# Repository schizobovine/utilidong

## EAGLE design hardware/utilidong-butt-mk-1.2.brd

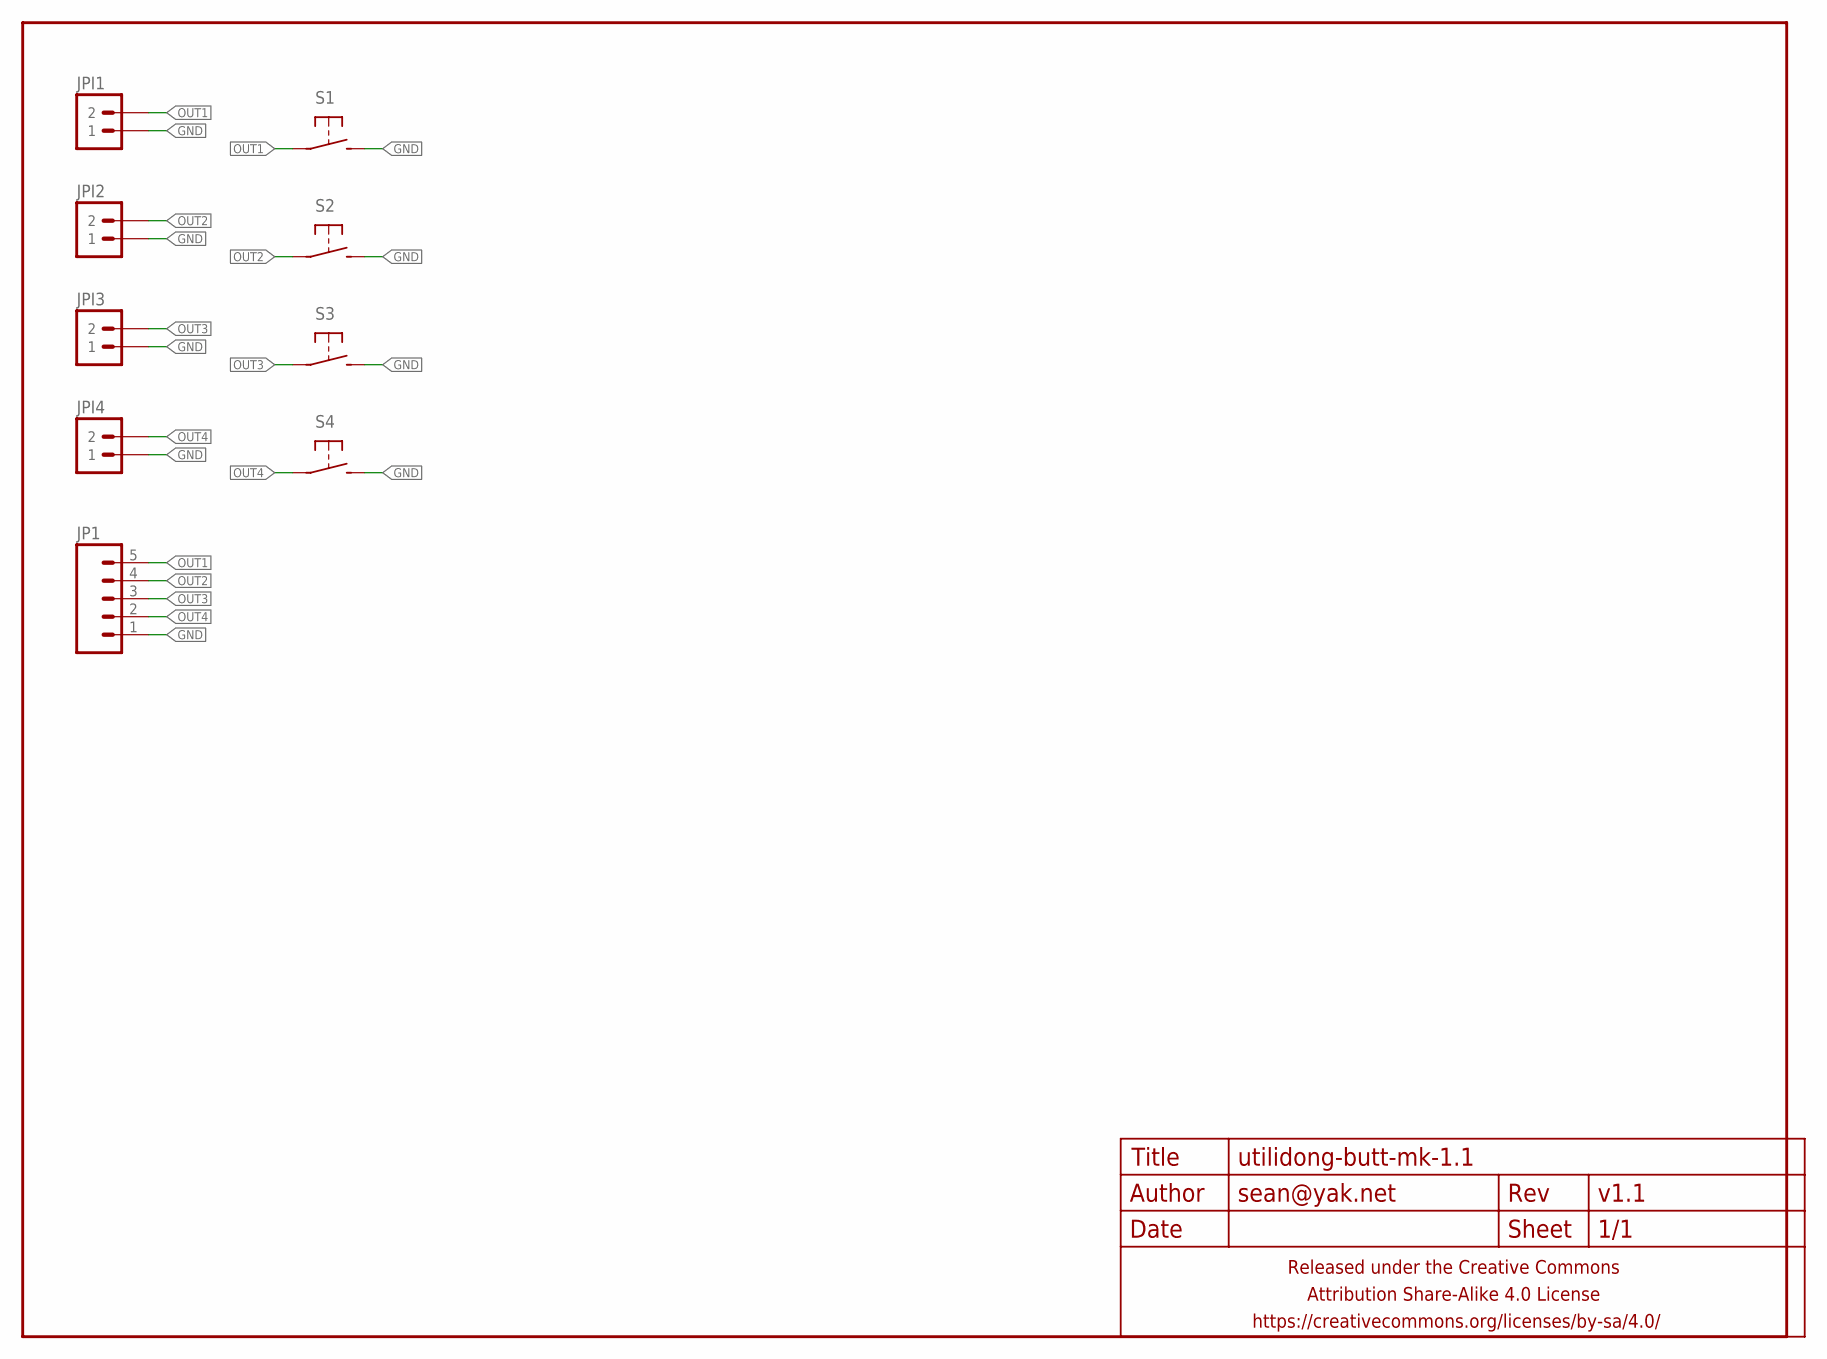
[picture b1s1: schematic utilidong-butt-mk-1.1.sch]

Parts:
FRAME1: FRAME-LETTERNO_PACKAGE; DUMMY
JP1: M05JST-PH-VERT-PTH; JST-5-PH-VERT-PTH
JPI1, JPI2, JPI3, JPI4: M02PTH-CENTERED; 1X02-CENTER
S1, S2, S3, S4: SPST-NO-TACT6MM-PTH-SMALL-PADS; DTS-6-SMALL-PADS

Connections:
GND: JP1.1, JPI1.1, JPI2.1, JPI3.1, JPI4.1, S1.3 (2), S1.4 (2), S2.3 (2), S2.4 (2), S3.3 (2), S3.4 (2), S4.3 (2), S4.4 (2)
OUT1: JP1.5, JPI1.2, S1.1, S1.2 (1)
OUT2: JP1.4, JPI2.2, S2.1, S2.2 (1)
OUT3: JP1.3, JPI3.2, S3.1, S3.2 (1)
OUT4: JP1.2, JPI4.2, S4.1, S4.2 (1)

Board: 2 copper layers, 10 parts (0 on the bottom side), 5 nets, no tracks yet.

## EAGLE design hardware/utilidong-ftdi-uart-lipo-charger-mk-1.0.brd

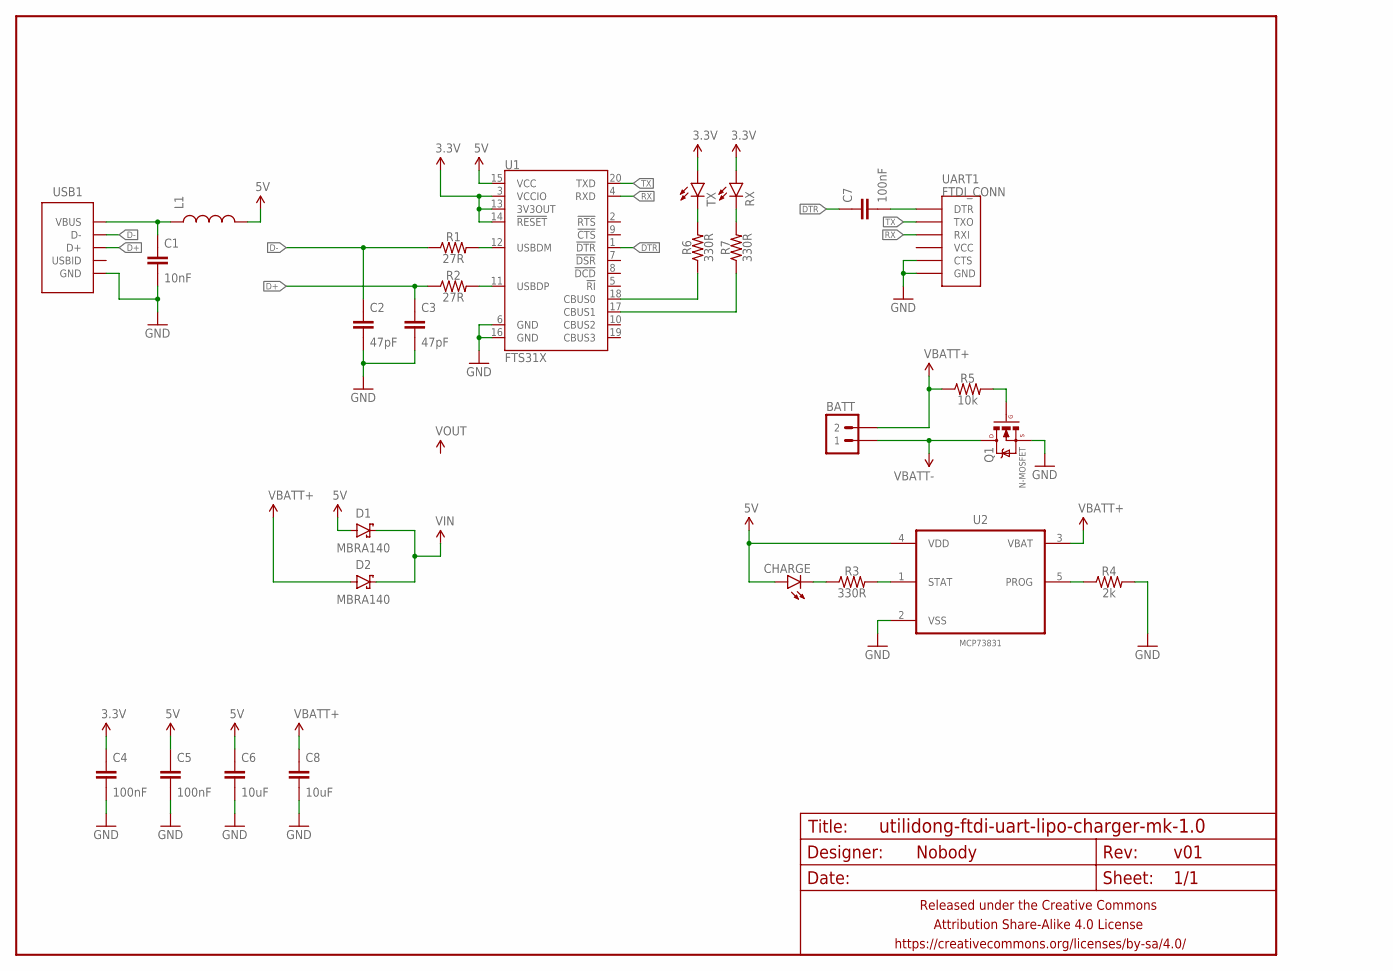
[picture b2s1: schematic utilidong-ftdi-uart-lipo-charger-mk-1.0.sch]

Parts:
BATT: M02PTH-CENTERED-R+; 1X02-CENTER-R+
C1: 10nF; C0805
C2, C3: 47pF; C0805
C4, C5, C7: 100nF; C0805
C6, C8: 10uF; C0805
CHARGE: LED1206; LED-1206
D1, D2: MBRA140; SMA-DIODE
FRAME1: FRAME-LETTERNO_PACKAGE; DUMMY
L1: INDUCTORL0805; L0805
Q1: N-MOSFET; SOT23
R1, R2: 27R; R0805
R3, R6, R7: 330R; R0805
R4: 2k; R0805
R5: 10k; R0805
RX: LED1206; LED-1206
TX: LED1206; LED-1206
U1: FTS31X; SSOP20_L
U2: MCP73831; SOT95P280X145-5N
UART1: FTDI_CONN
USB1: USB-ABCOMBO; USB-MICRO-B-FCI-CUTOUT

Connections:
3.3V: C4.1, RX.A, TX.A, U1.3 (VCCIO), U1.13 (3V3OUT), U1.14 (!RESET)
5V: C5.1, C6.1, CHARGE.A, D1.A, L1.2, U1.15 (VCC), U2.4 (VDD)
D+: C3.1, R2.1, USB1.3 (D+)
D-: C2.1, R1.1, USB1.2 (D-)
DTR: C7.1, U1.1 (!DTR)
GND: C1.2, C2.2, C3.2, C4.2, C5.2, C6.2, C8.2, Q1.2 (S), R4.2, U1.6 (GND), U1.16 (GND), U2.2 (VSS), UART1.CTS, UART1.GND, USB1.5 (GND), USB1.P$1 (GND), USB1.P$2 (GND)
unnamed: R1.2, U1.12 (USBDM)
unnamed: R2.2, U1.11 (USBDP)
unnamed: C1.1, L1.1, USB1.1 (VBUS)
unnamed: C7.2, UART1.DTR
unnamed: R3.2, U2.1 (STAT)
unnamed: CHARGE.C, R3.1
unnamed: R6.1, U1.18 (CBUS0)
unnamed: R4.1, U2.5 (PROG)
unnamed: R6.2, TX.C
unnamed: R7.2, RX.C
unnamed: Q1.1 (G), R5.2
unnamed: R7.1, U1.17 (CBUS1)
RX: U1.4 (RXD), UART1.RXI
TX: U1.20 (TXD), UART1.TXO
VBATT+: BATT.2, C8.1, D2.A, R5.1, U2.3 (VBAT)
VBATT-: BATT.1, Q1.3 (D)
VIN: D1.C, D2.C

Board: 2 copper layers, 28 parts (0 on the bottom side), 23 nets, no tracks yet.

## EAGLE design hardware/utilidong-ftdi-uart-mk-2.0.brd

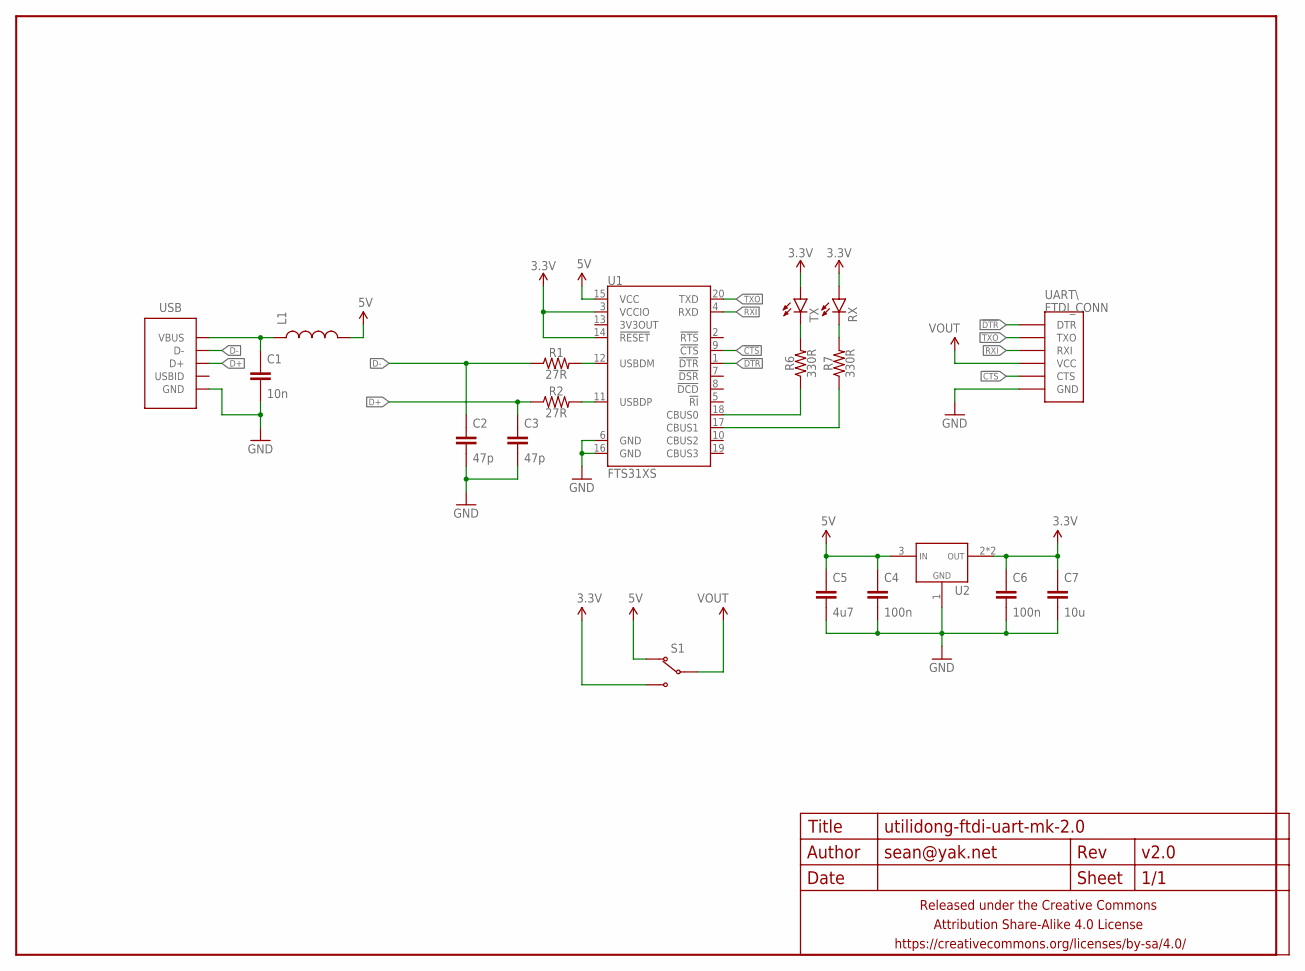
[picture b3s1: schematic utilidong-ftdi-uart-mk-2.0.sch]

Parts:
C1: 10n; C0603
C2, C3: 47p; C0603
C4, C6: 100n; C0603
C5: 4u7; C0603
C7: 10u; C0805
FRAME1: FRAME-LETTERNO_PACKAGE; DUMMY
L1: INDUCTOR0603; 0603
R1, R2: 27R; R0603
R6, R7: 330R; R0603
RX: LED0603; LED-0603
S1: SWITCH-SPDTSMD-RA; SWITCH-SPDT-SMD-RA
TX: LED0603; LED-0603
U1: FTS31XS; SSOP20_L
U2: VREG_1117SOT89; SOT89
UART\: FTDI_CONN
USB: USB-ABFCI-10103594-USB-MICRO-B-LESS; FCI-10103594-USB-MICRO-B-LESS

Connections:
3.3V: C6.1, C7.1, RX.A, S1.1 (NO), TX.A, U1.3 (VCCIO), U1.14 (!RESET), U2.2 (VOUT), U2.4 (VOUT)
5V: C4.1, C5.1, L1.2, S1.3 (NC), U1.15 (VCC), U2.3 (VIN)
!CTS: U1.9 (!CTS), UART\.CTS
!DTR: U1.1 (!DTR), UART\.DTR
D+: C3.1, R2.1, USB.3 (D+)
D-: C2.1, R1.1, USB.2 (D-)
GND: C1.2, C2.2, C3.2, C4.2, C5.2, C6.2, C7.2, U1.6 (GND), U1.16 (GND), U2.1 (GND), UART\.GND, USB.5 (GND)
unnamed: R1.2, U1.12 (USBDM)
unnamed: R2.2, U1.11 (USBDP)
unnamed: C1.1, L1.1, USB.1 (VBUS)
unnamed: R6.1, U1.18 (CBUS0)
unnamed: R6.2, TX.C
unnamed: R7.2, RX.C
unnamed: R7.1, U1.17 (CBUS1)
RXI: U1.4 (RXD), UART\.RXI
TXO: U1.20 (TXD), UART\.TXO
VOUT: S1.2 (COM), UART\.VCC

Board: 2 copper layers, 23 parts (3 on the bottom side), 17 nets, no tracks yet.

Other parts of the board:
U$3: COW_SMALL
U$4: CC-BY-SA-4.0-NO-URL
U$6: OSHWLOGO_TOP_0.2_A

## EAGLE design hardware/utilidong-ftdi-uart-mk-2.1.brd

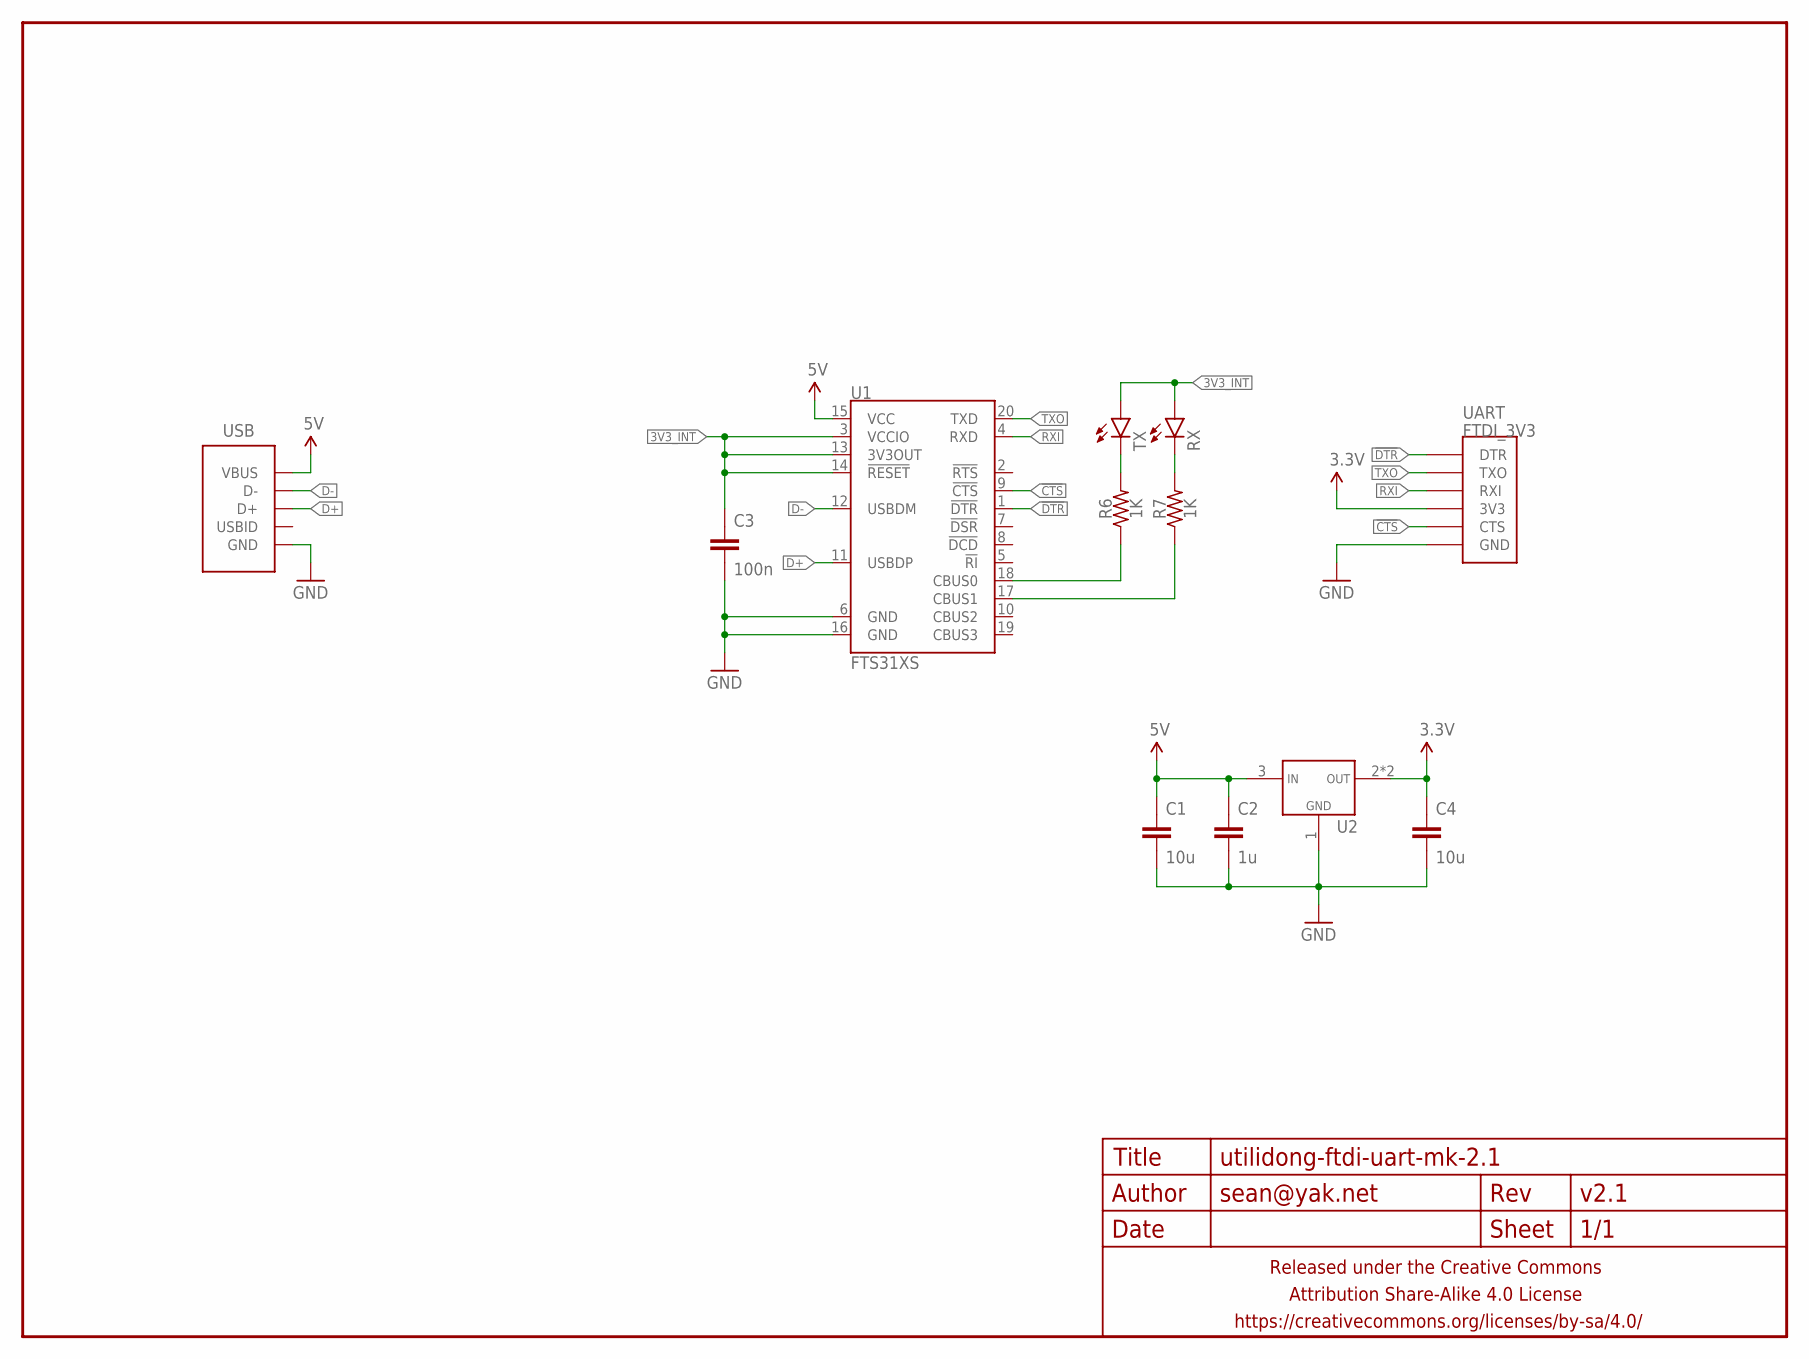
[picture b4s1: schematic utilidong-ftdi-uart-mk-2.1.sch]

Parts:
C1, C4: 10u; C0805
C2: 1u; C0603
C3: 100n; C0603
FRAME1: FRAME-LETTERNO_PACKAGE; DUMMY
R6, R7: 1K; R0603
RX: LED0603; LED-0603
TX: LED0603; LED-0603
U1: FTS31XS; SSOP20_L
U2: VREG_1117SOT89; SOT89
UART: FTDI_3V3
USB: USB-ABFCI-10103594-USB-MICRO-B-LESS; FCI-10103594-USB-MICRO-B-LESS

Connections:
3.3V: C4.1, U2.2 (VOUT), U2.4 (VOUT), UART.P$4 (3V3)
3V3_INT: C3.1, RX.A, TX.A, U1.3 (VCCIO), U1.13 (3V3OUT), U1.14 (!RESET)
5V: C1.1, C2.1, U1.15 (VCC), U2.3 (VIN), USB.1 (VBUS)
!CTS: U1.9 (!CTS), UART.P$5 (CTS)
!DTR: U1.1 (!DTR), UART.P$1 (DTR)
D+: U1.11 (USBDP), USB.3 (D+)
D-: U1.12 (USBDM), USB.2 (D-)
GND: C1.2, C2.2, C3.2, C4.2, U1.6 (GND), U1.16 (GND), U2.1 (GND), UART.P$6 (GND), USB.5 (GND)
unnamed: R6.1, U1.18 (CBUS0)
unnamed: R6.2, TX.C
unnamed: R7.2, RX.C
unnamed: R7.1, U1.17 (CBUS1)
RXI: U1.4 (RXD), UART.P$3 (RXI)
TXO: U1.20 (TXD), UART.P$2 (TXO)

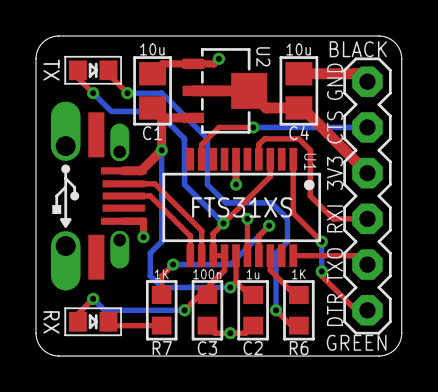
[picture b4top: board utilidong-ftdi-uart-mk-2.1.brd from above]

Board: 2 copper layers, 20.3 x 17.8 mm, 14 parts (1 on the bottom side), 14 nets.

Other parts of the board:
U$3: COW_SMALL

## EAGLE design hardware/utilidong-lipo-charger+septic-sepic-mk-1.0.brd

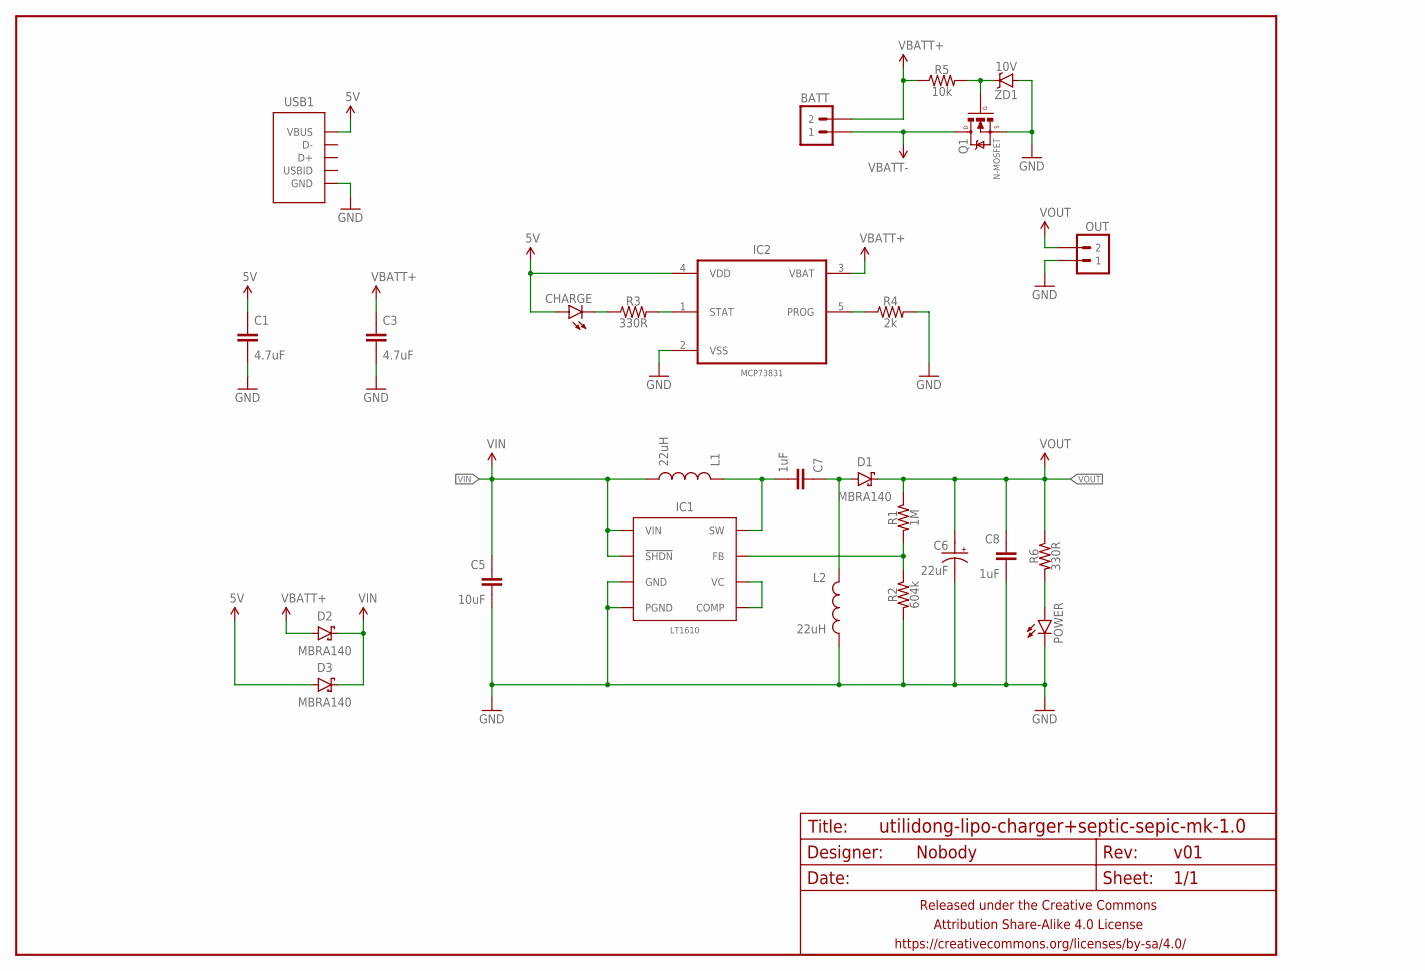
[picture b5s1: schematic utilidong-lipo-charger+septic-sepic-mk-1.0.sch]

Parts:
BATT: M02PTH-CENTERED-R+; 1X02-CENTER-R+
C1, C3: 4.7uF; C0805
C5: 10uF; C0805
C6: 22uF; E2,5-6
C7, C8: 1uF; C0805
CHARGE: LED1206; LED-1206
D1: MBRA140; SMA-DIODE-SCHOTTKY
D2, D3: MBRA140; SMA-DIODE
FRAME1: FRAME-LETTERNO_PACKAGE; DUMMY
IC1: LT1610; SO08
IC2: MCP73831; SOT95P280X145-5N
L1, L2: 22uH; TAIYO-YUDEN-40XX
OUT: M02PTH-CENTERED-R+; 1X02-CENTER-R+
POWER: LED1206; LED-1206
Q1: N-MOSFET; SOT23
R1: 1M; R0805
R2: 604k; R0805
R3, R6: 330R; R0805
R4: 2k; R0805
R5: 10k; R0805
USB1: USB-ABCOMBO; USB-MICRO-B-FCI-CUTOUT
ZD1: 10V; SOD123-ZENER

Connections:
5V: C1.1, CHARGE.A, D3.A, IC2.4 (VDD), USB1.1 (VBUS)
GND: C1.2, C3.2, C5.2, C6.-, C8.2, IC1.4 (PGND), IC1.7 (GND), IC2.2 (VSS), L2.2, OUT.1, POWER.C, Q1.2 (S), R2.2, R4.2, USB1.5 (GND), USB1.P$1 (GND), USB1.P$2 (GND), ZD1.A
unnamed: C7.1, D1.A, L2.1
unnamed: C7.2, IC1.5 (SW), L1.1
unnamed: POWER.A, R6.2
unnamed: IC1.1 (VC), IC1.8 (COMP)
unnamed: IC2.1 (STAT), R3.2
unnamed: CHARGE.C, R3.1
unnamed: IC1.2 (FB), R1.2, R2.1
unnamed: IC2.5 (PROG), R4.1
unnamed: Q1.1 (G), R5.2, ZD1.C
VBATT+: BATT.2, C3.1, D2.A, IC2.3 (VBAT), R5.1
VBATT-: BATT.1, Q1.3 (D)
VIN: C5.1, D2.C, D3.C, IC1.3 (!SHDN), IC1.6 (VIN), L1.2
VOUT: C6.+, C8.1, D1.C, OUT.2, R1.1, R6.1

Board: 2 copper layers, 29 parts (2 on the bottom side), 15 nets, no tracks yet.

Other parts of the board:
U$8: CC-BY-SA-4.0-NO-URL
U$9: COW_SMALL_METAL

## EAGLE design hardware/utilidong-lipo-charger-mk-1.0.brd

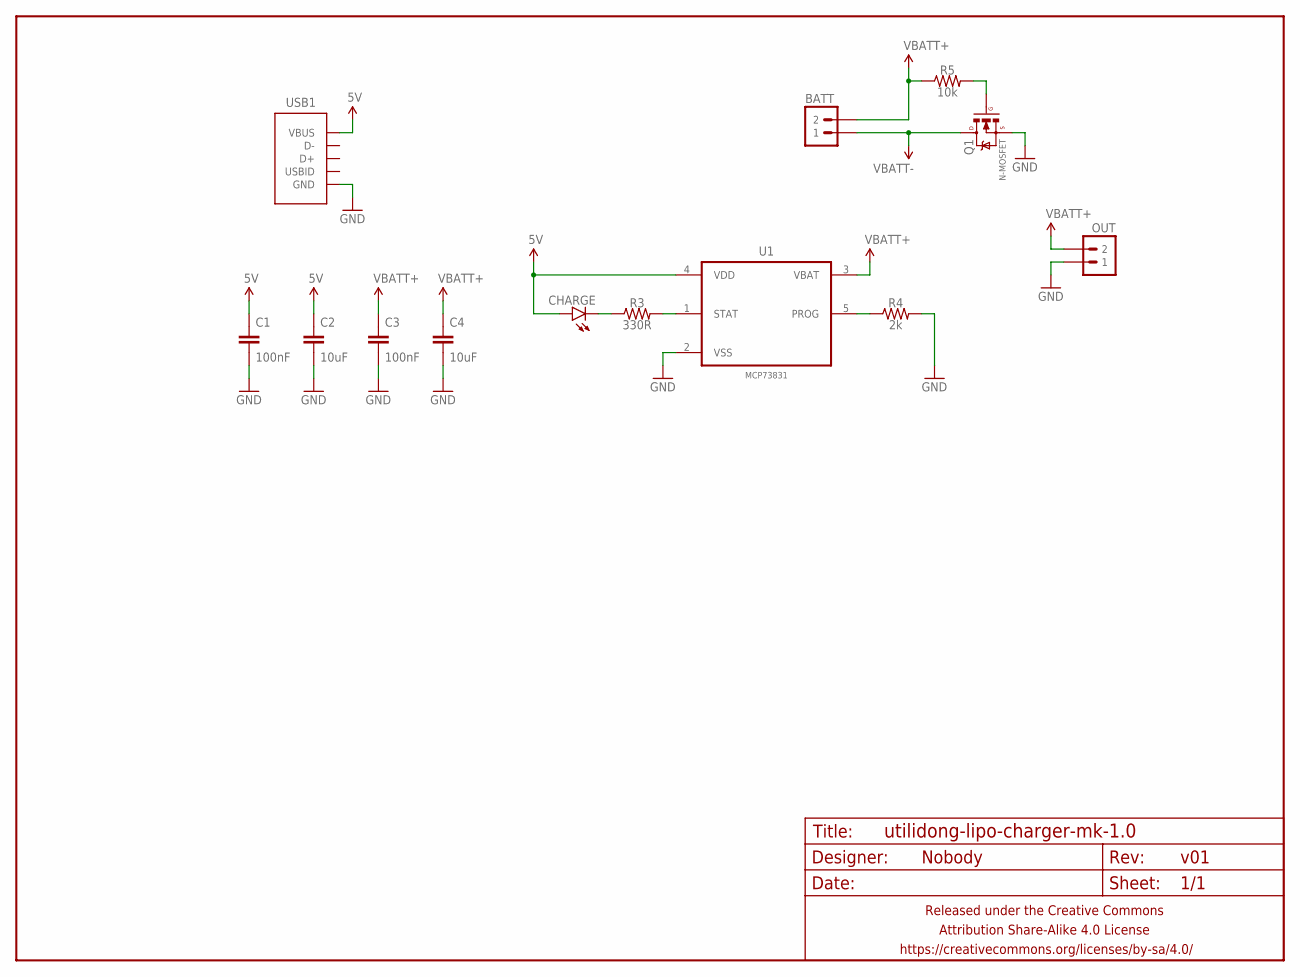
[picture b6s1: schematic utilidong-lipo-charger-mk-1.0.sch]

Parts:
BATT: M02PTH-CENTERED-R+; 1X02-CENTER-R+
C1, C3: 100nF; C0805
C2, C4: 10uF; C1206
CHARGE: LED1206; LED-1206
FRAME1: FRAME-LETTERNO_PACKAGE; DUMMY
OUT: M02PTH-CENTERED-R+; 1X02-CENTER-R+
Q1: N-MOSFET; SOT23
R3: 330R; R0805
R4: 2k; R0805
R5: 10k; R0805
U1: MCP73831; SOT95P280X145-5N
USB1: USB-ABCOMBO; USB-MICRO-B-FCI-CUTOUT

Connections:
5V: C1.1, C2.1, CHARGE.A, U1.4 (VDD), USB1.1 (VBUS)
GND: C1.2, C2.2, C3.2, C4.2, OUT.1, Q1.2 (S), R4.2, U1.2 (VSS), USB1.5 (GND), USB1.P$1 (GND), USB1.P$2 (GND)
unnamed: R3.2, U1.1 (STAT)
unnamed: CHARGE.C, R3.1
unnamed: R4.1, U1.5 (PROG)
unnamed: Q1.1 (G), R5.2
VBATT+: BATT.2, C3.1, C4.1, OUT.2, R5.1, U1.3 (VBAT)
VBATT-: BATT.1, Q1.3 (D)

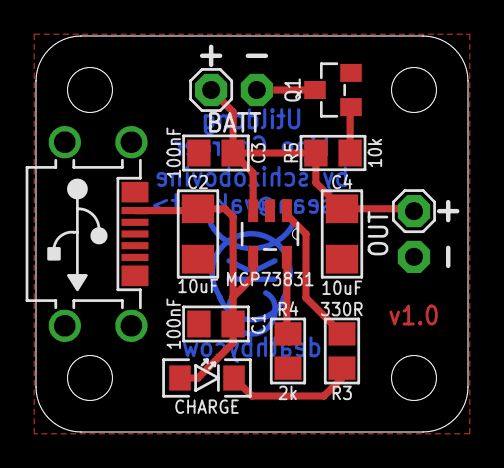
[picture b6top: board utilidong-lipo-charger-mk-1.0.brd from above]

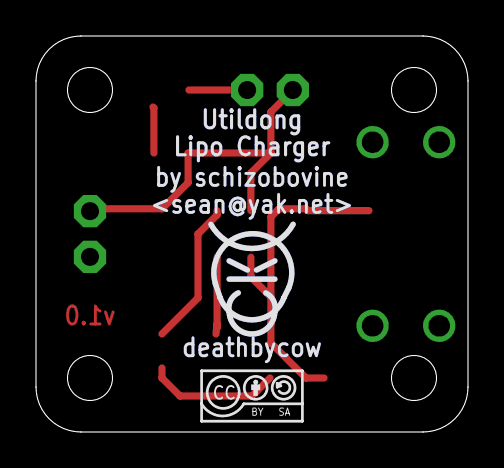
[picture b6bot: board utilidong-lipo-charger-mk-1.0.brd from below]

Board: 2 copper layers, 24.0 x 22.0 mm, 16 parts (2 on the bottom side), 8 nets.

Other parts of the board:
U$8: CC-BY-SA-4.0-NO-URL
U$9: COW_SMALL_METAL

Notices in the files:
parts and their libraries:
A_butts: Released under the Creative Commons Attribution Share-Alike 4.0 License
A_butts: https://creativecommons.org/licenses/by-sa/4.0
A_butts: Released under the Creative Commons
